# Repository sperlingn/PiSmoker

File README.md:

# PiSmoker

##Dependencies
* RPI.GPIO
* spidev
* [Adafruit_Python_CharLCD](https://github.com/adafruit/Adafruit_Python_CharLCD)
* [Python-firebase](https://github.com/ozgur/python-firebase) Use github version instead of pip

## Schematics and Boards
* PiSmoker_pwr_triac_isol -- AC handling board, includes SW PS for backpowering Raspi.
* PiSmoker_sig_v1.1 -- Signal boards, conforms to Pi HAT specifications, including EEPROM.

Signal board and power board for traic based control.  Includes board power with isolation and 4 triacs.  Signaling board has space for 1 RTD via MAX31865, 2 thermocouples (and internal temperature sensor) via ADS1118, and 2 thermocouples and 4 thermistor probes via MCP3208.  Using MAX31865 temperature for CJC for all thermocouples should be possible due to placement underneath connector.

## Work to be done

* TODO: Add support for firebox burnout sensor (purpose of TC1, hotbox TC to see if temp is >setpoint, will require testing temps).  Should be able to run igniter if it is sensed early enough without having to clear out the firebox of pellets or blow the temperature range.
* TODO: Add parsing of EEPROM settings.

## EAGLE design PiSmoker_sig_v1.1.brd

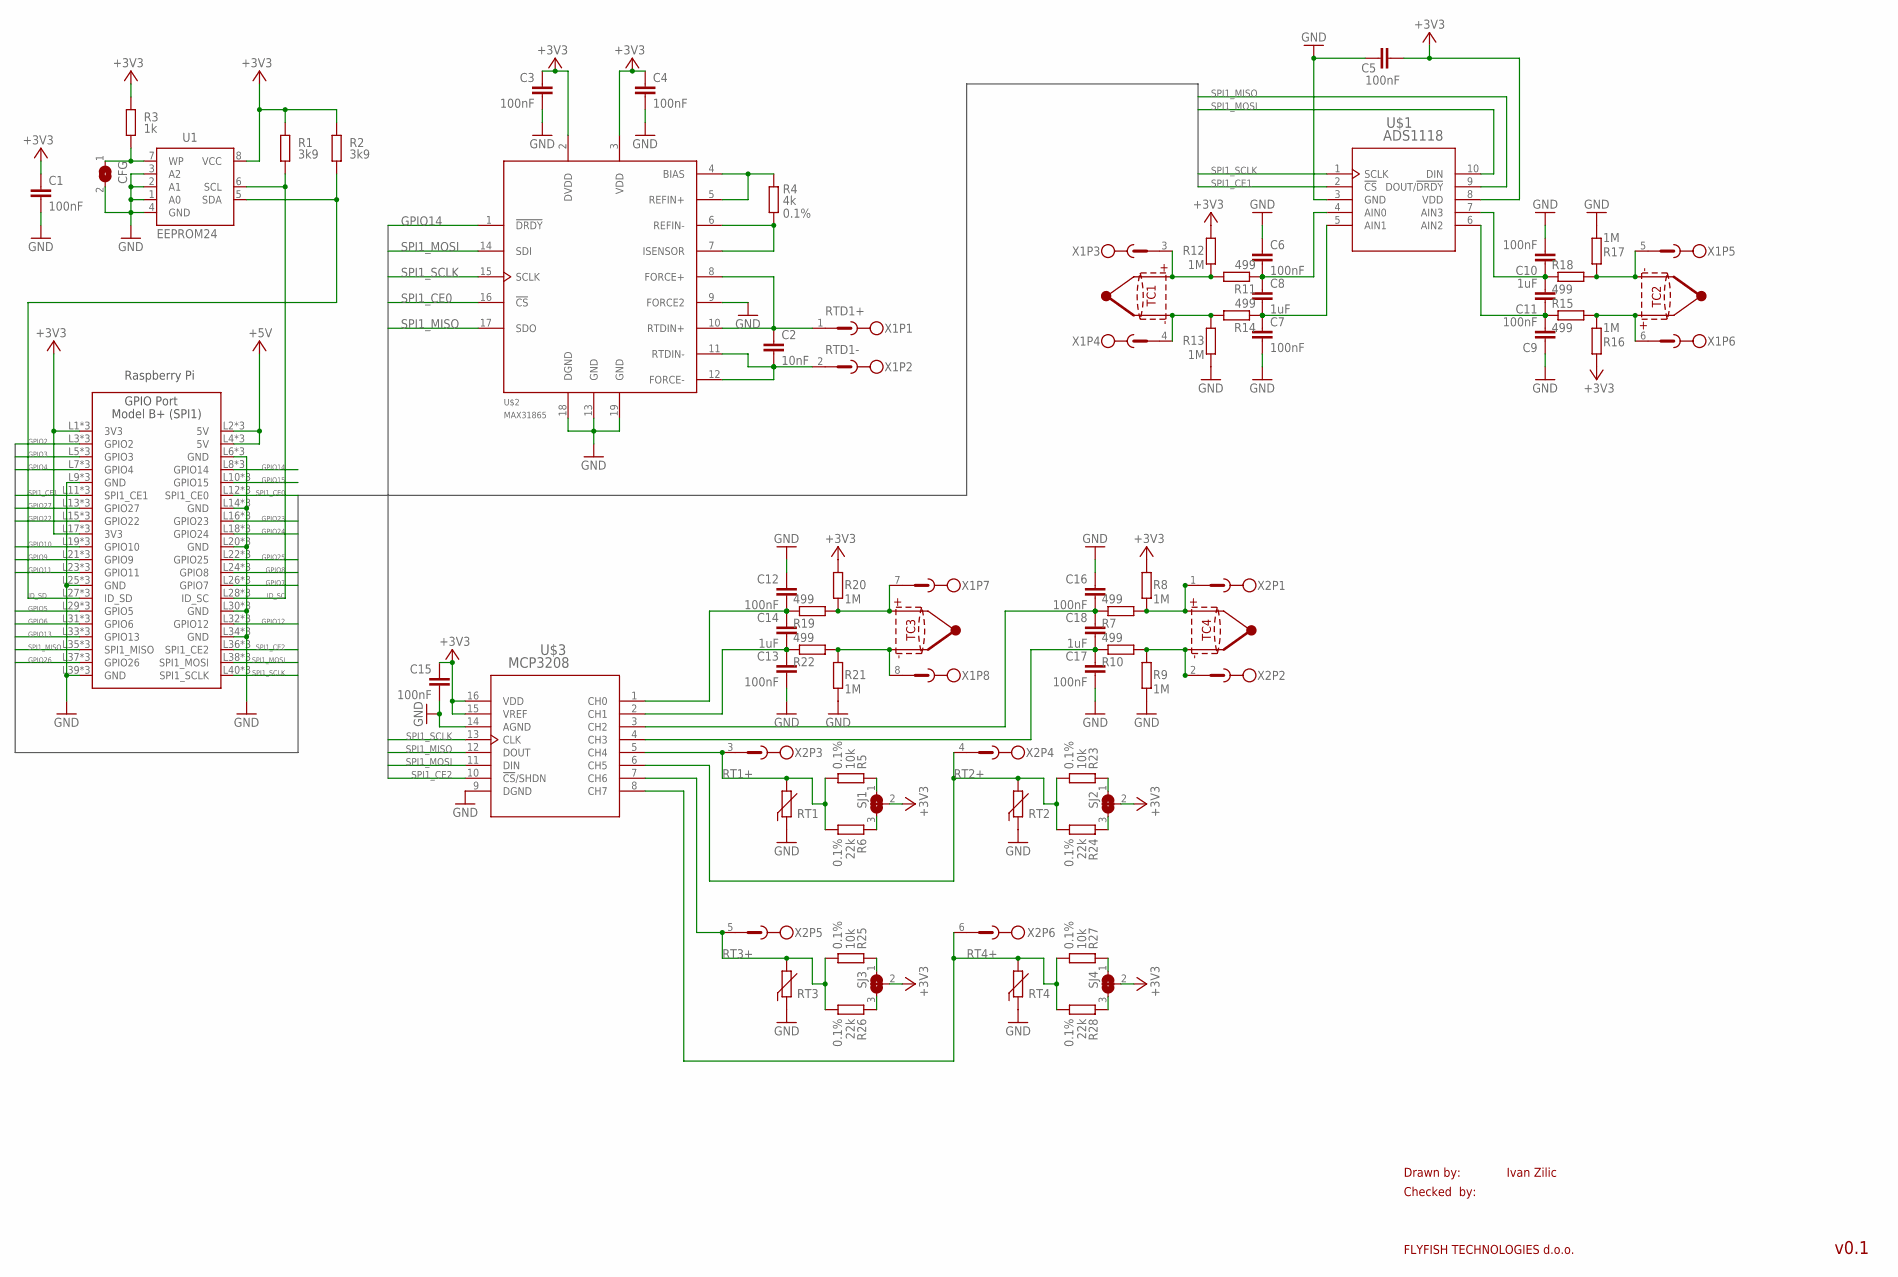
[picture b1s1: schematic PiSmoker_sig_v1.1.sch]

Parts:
C1, C3, C4, C5, C6, C7, C9, C10, C12, C13, C15, C16, C17: 100nF; C0805K
C2: 10nF; C0805
C8, C11, C14, C18: 1uF; C0805K
CFG: SOLDERJUMPERCLOSED; SOLDERJUMPER_CLOSEDWIRE
R1, R2: 3k9; M0805; TOLERANCE 5%
R3: 1k; M0805; TOLERANCE 5%
R4: 4k; R1206; TOLERANCE 0.1%
R5, R23, R25, R27: 10k; R0805; TOLERANCE 0.1%
R6, R24, R26, R28: 22k; R0805; TOLERANCE 0.1%
R7, R10, R11, R14, R15, R18, R19, R22: 499; M0805; TOLERANCE 5%
R8, R9, R12, R13, R16, R17, R20, R21: 1M; M0805; TOLERANCE 5%
SJ1, SJ2, SJ3, SJ4: SOLDERJUMPER_2WAY; SOLDERJUMPER_2WAY_ARROW_NOPASTE
U1: EEPROM24; SOIC8
U$1: ADS1118; DGS10
U$2: MAX31865; SSOP20_A20-1
U$3: MCP3208; SOIC16-N_MC
X1: TERMINAL_BLOCK-8PTSM0,5; PHOENIX_PTSM0,5/8-2,5-H_SMD_R44
X2: PHOENIX_PTS1,5-6PTSM0,5; PHOENIX_PTSM0,5/6-2,5-H_SMD_R44
X3: RASPI_GPIO_3B_SPI1_M20-781LOWER-876_UPPER; M20-781_SMD_LOWER_876_UPPER

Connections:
+3V3: C1.1, C3.1, C4.1, C5.2, C15.1, R1.2, R2.2, R3.2, R8.1, R12.1, R16.1, R20.1, SJ1.2, SJ2.2, SJ3.2, SJ4.2, U1.8 (VCC), U$1.8 (VDD), U$2.2 (DVDD), U$2.3 (VDD), U$3.15 (VREF), U$3.16 (VDD), X3.L1 (3V3), X3.L17 (3V3), X3.P1 (3V3), X3.P17 (3V3), X3.U1 (3V3), X3.U17 (3V3)
+5V: X3.L2 (5V), X3.L4 (5V), X3.P2 (5V), X3.P4 (5V), X3.U2 (5V), X3.U4 (5V)
GND: C1.2, C3.2, C4.2, C5.1, C6.1, C7.2, C9.1, C10.2, C12.1, C13.2, C15.2, C16.1, C17.2, CFG.2, R9.2, R13.2, R17.2, R21.2, U1.1 (A0), U1.2 (A1), U1.3 (A2), U1.4 (GND), U$1.3 (GND), U$2.9 (FORCE2), U$2.13 (GND), U$2.18 (DGND), U$2.19 (GND), U$3.9 (DGND), U$3.14 (AGND), X3.L6 (GND), X3.L9 (GND), X3.L14 (GND), X3.L20 (GND), X3.L25 (GND), X3.L30 (GND), X3.L34 (GND), X3.L39 (GND), X3.P6 (GND), X3.P9 (GND), X3.P14 (GND), X3.P20 (GND), X3.P25 (GND), X3.P30 (GND), X3.P34 (GND), X3.P39 (GND), X3.U6 (GND), X3.U9 (GND), X3.U14 (GND), X3.U20 (GND), X3.U25 (GND), X3.U30 (GND), X3.U34 (GND), X3.U39 (GND)
GPIO2: X3.L3 (GPIO2), X3.P3 (GPIO2), X3.U3 (GPIO2)
GPIO3: X3.L5 (GPIO3), X3.P5 (GPIO3), X3.U5 (GPIO3)
GPIO4: X3.L7 (GPIO4), X3.P7 (GPIO4), X3.U7 (GPIO4)
GPIO5: X3.L29 (GPIO5), X3.P29 (GPIO5), X3.U29 (GPIO5)
GPIO6: X3.L31 (GPIO6), X3.P31 (GPIO6), X3.U31 (GPIO6)
GPIO7: X3.L26 (GPIO7), X3.P26 (GPIO7), X3.U26 (GPIO7)
GPIO8: X3.L24 (GPIO8), X3.P24 (GPIO8), X3.U24 (GPIO8)
GPIO9: X3.L21 (GPIO9), X3.P21 (GPIO9), X3.U21 (GPIO9)
GPIO10: X3.L19 (GPIO10), X3.P19 (GPIO10), X3.U19 (GPIO10)
GPIO11: X3.L23 (GPIO11), X3.P23 (GPIO11), X3.U23 (GPIO11)
GPIO12: X3.L32 (GPIO12), X3.P32 (GPIO12), X3.U32 (GPIO12)
GPIO13: X3.L33 (GPIO13), X3.P33 (GPIO13), X3.U33 (GPIO13)
GPIO14: U$2.1 (!DRDY), X3.L8 (GPIO14), X3.P8 (GPIO14), X3.U8 (GPIO14)
GPIO15: X3.L10 (GPIO15), X3.P10 (GPIO15), X3.U10 (GPIO15)
GPIO22: X3.L15 (GPIO22), X3.P15 (GPIO22), X3.U15 (GPIO22)
GPIO23: X3.L16 (GPIO23), X3.P16 (GPIO23), X3.U16 (GPIO23)
GPIO24: X3.L18 (GPIO24), X3.P18 (GPIO24), X3.U18 (GPIO24)
GPIO25: X3.L22 (GPIO25), X3.P22 (GPIO25), X3.U22 (GPIO25)
GPIO26: X3.L37 (GPIO26), X3.P37 (GPIO26), X3.U37 (GPIO26)
GPIO27: X3.L13 (GPIO27), X3.P13 (GPIO27), X3.U13 (GPIO27)
ID_SC: R1.1, U1.6 (SCL), X3.L28 (ID_SC), X3.P28 (ID_SC), X3.U28 (ID_SC)
ID_SD: R2.1, U1.5 (SDA), X3.L27 (ID_SD), X3.P27 (ID_SD), X3.U27 (ID_SD)
unnamed: C7.1, C8.2, R14.1, U$1.5 (AIN1)
unnamed: C6.2, C8.1, R11.1, U$1.4 (AIN0)
unnamed: CFG.1, R3.1, U1.7 (WP)
unnamed: R5.2, SJ1.1
unnamed: R6.2, SJ1.3
unnamed: C17.1, C18.2, R10.1, U$3.4 (CH3)
unnamed: C16.2, C18.1, R7.1, U$3.3 (CH2)
unnamed: R23.2, SJ2.1
unnamed: R24.2, SJ2.3
unnamed: R25.2, SJ3.1
unnamed: R4.2, U$2.4 (BIAS), U$2.5 (REFIN+)
unnamed: R4.1, U$2.6 (REFIN-), U$2.7 (ISENSOR)
unnamed: C13.1, C14.2, R22.1, U$3.2 (CH1)
unnamed: C12.2, C14.1, R19.1, U$3.1 (CH0)
unnamed: C10.1, C11.2, R18.1, U$1.7 (AIN3)
unnamed: C9.2, C11.1, R15.1, U$1.6 (AIN2)
unnamed: R26.2, SJ3.3
unnamed: R27.2, SJ4.1
unnamed: R28.2, SJ4.3
RT1+: R5.1, R6.1, U$3.5 (CH4), X2.3
RT2+: R23.1, R24.1, U$3.6 (CH5), X2.4
RT3+: R25.1, R26.1, U$3.7 (CH6), X2.5
RT4+: R27.1, R28.1, U$3.8 (CH7), X2.6
RTD1+: C2.1, U$2.8 (FORCE+), U$2.10 (RTDIN+), X1.1
RTD1-: C2.2, U$2.11 (RTDIN-), U$2.12 (FORCE-), X1.2
SPI1_CE0: U$2.16 (!CS), X3.L12 (SPI1_CE0), X3.P12 (SPI1_CE0), X3.U12 (SPI1_CE0)
SPI1_CE1: U$1.2 (!CS), X3.L11 (SPI1_CE1), X3.P11 (SPI1_CE1), X3.U11 (SPI1_CE1)
SPI1_CE2: U$3.10 (!CS!/SHDN), X3.L36 (SPI1_CE2), X3.P36 (SPI1_CE2), X3.U36 (SPI1_CE2)
SPI1_MISO: U$1.9 (DOUT/!DRDY), U$2.17 (SDO), U$3.12 (DOUT), X3.L35 (SPI1_MISO), X3.P35 (SPI1_MISO), X3.U35 (SPI1_MISO)
SPI1_MOSI: U$1.10 (DIN), U$2.14 (SDI), U$3.11 (DIN), X3.L38 (SPI1_MOSI), X3.P38 (SPI1_MOSI), X3.U38 (SPI1_MOSI)
SPI1_SCLK: U$1.1 (SCLK), U$2.15 (SCLK), U$3.13 (CLK), X3.L40 (SPI1_SCLK), X3.P40 (SPI1_SCLK), X3.U40 (SPI1_SCLK)
TC1+: R11.2, R12.2, X1.3
TC1-: R13.1, R14.2, X1.4
TC2+: R17.1, R18.2, X1.5
TC2-: R15.2, R16.2, X1.6
TC3+: R19.2, R20.2, X1.7
TC3-: R21.1, R22.2, X1.8
TC4+: R7.2, R8.2, X2.1
TC4-: R9.1, R10.2, X2.2

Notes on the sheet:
Drawn by:
Checked by:
FLYFISH TECHNOLOGIES d.o.o.
Ivan Zilic
v0.1

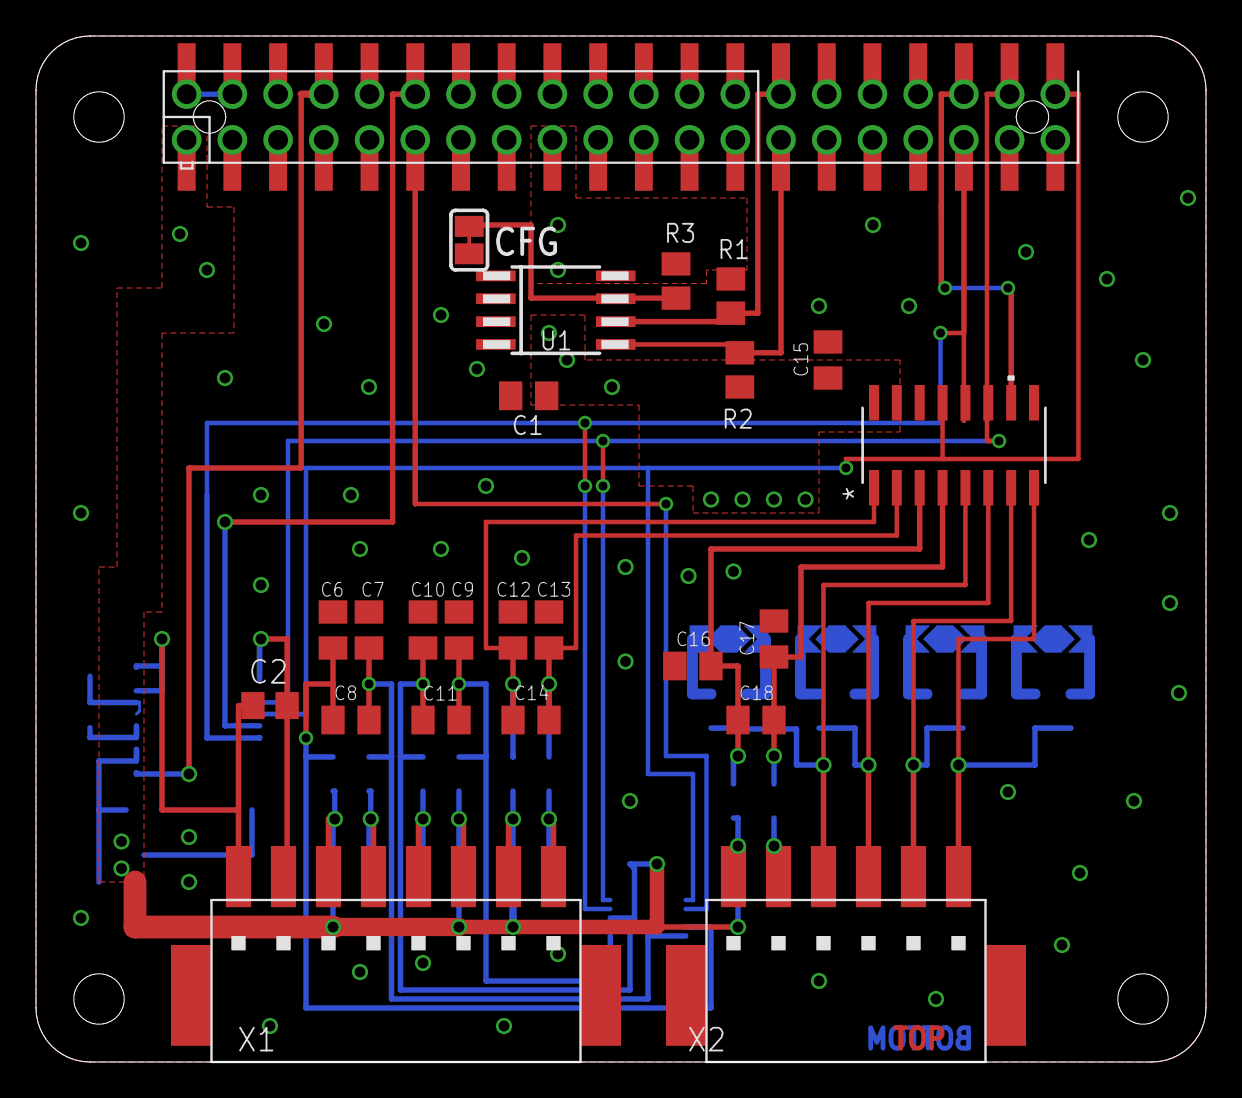
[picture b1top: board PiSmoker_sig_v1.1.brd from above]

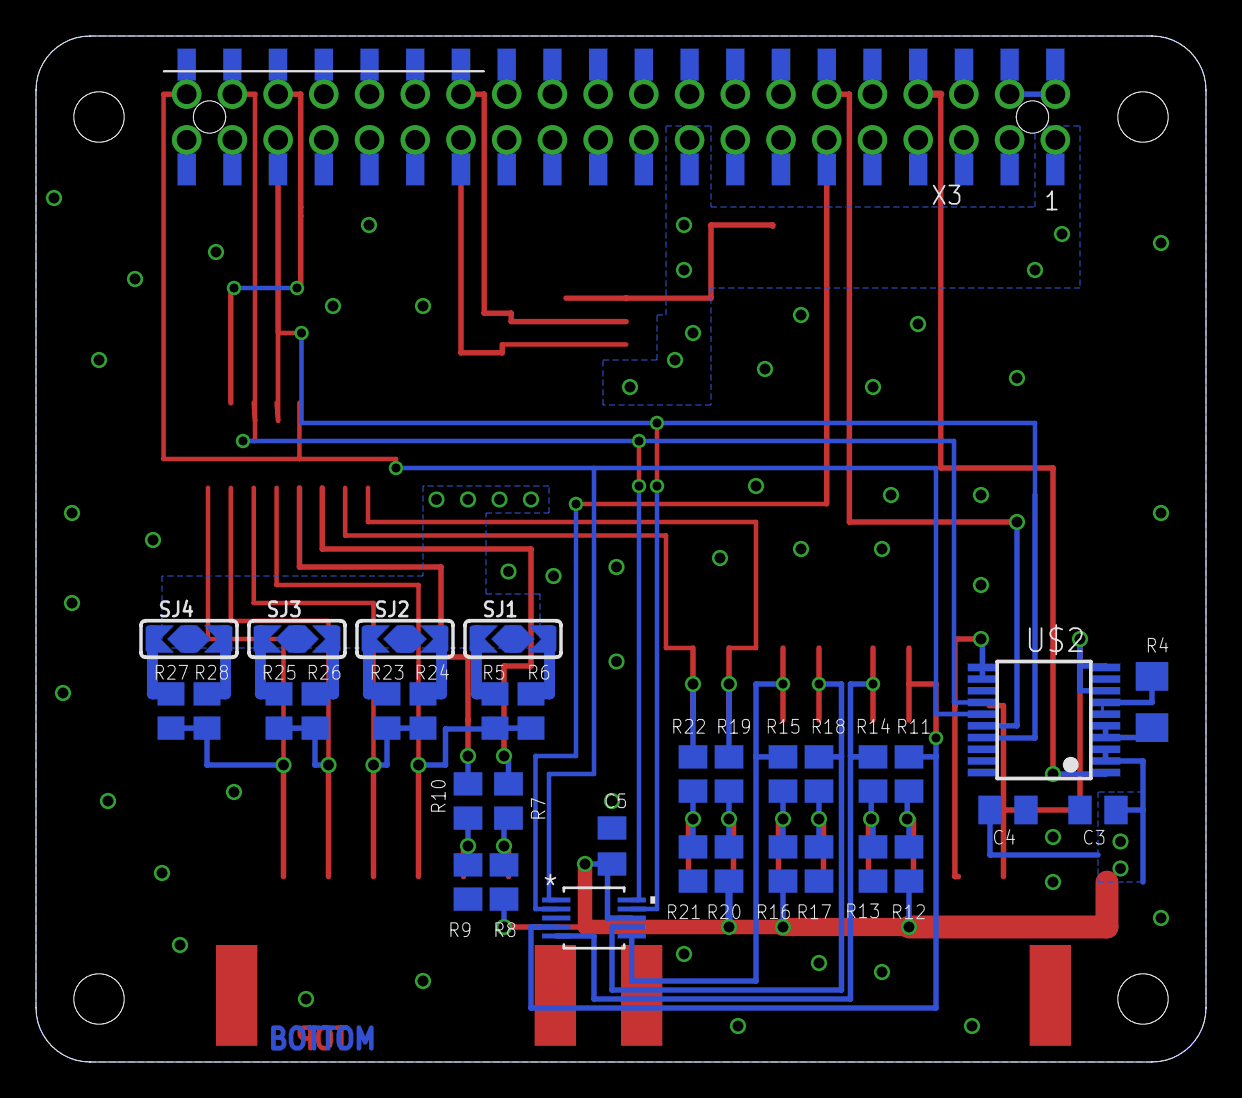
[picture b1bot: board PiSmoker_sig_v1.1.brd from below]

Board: 2 copper layers, 65.0 x 57.0 mm, 58 parts (34 on the bottom side), 64 nets.

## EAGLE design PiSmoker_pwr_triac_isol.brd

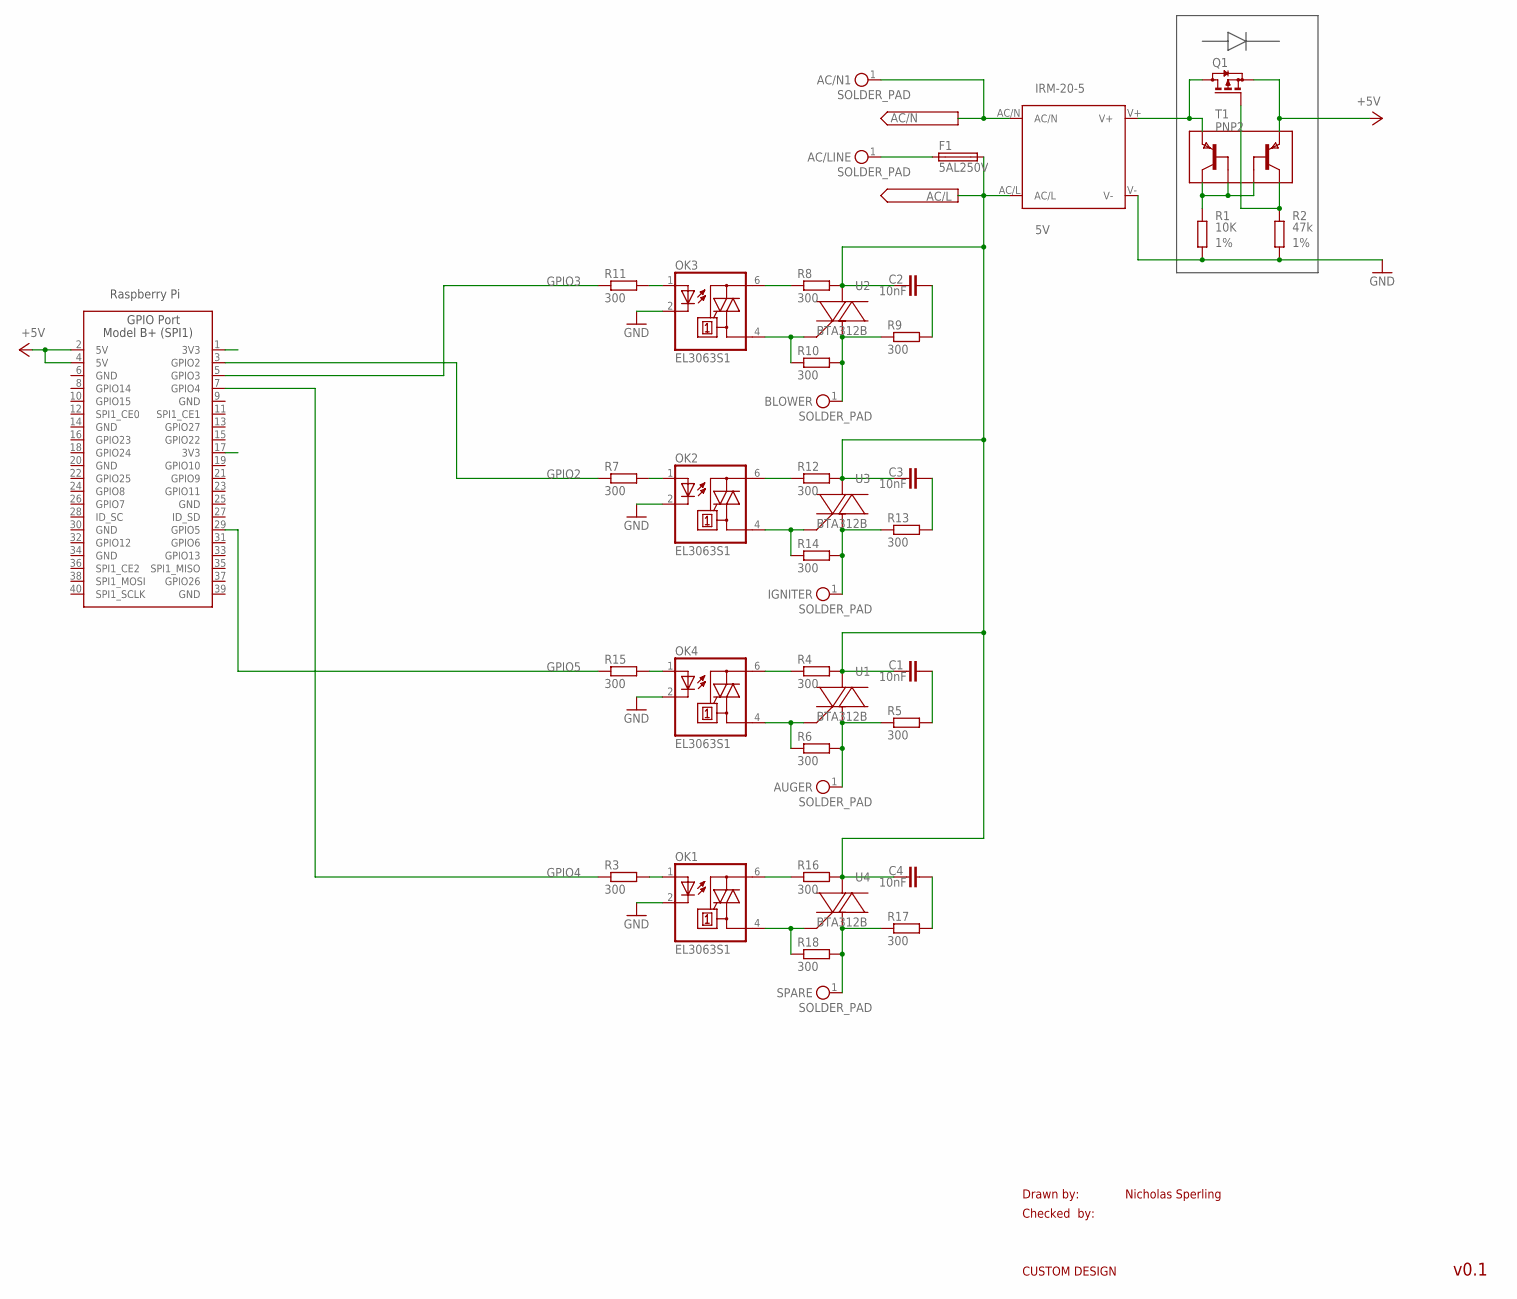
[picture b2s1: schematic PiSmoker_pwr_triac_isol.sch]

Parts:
AC/LINE: SOLDER_PAD; SOLDER_PAD_18AWG
AC/N1: SOLDER_PAD; SOLDER_PAD_18AWG
AUGER: SOLDER_PAD; SOLDER_PAD_18AWG
BLOWER: SOLDER_PAD; SOLDER_PAD_18AWG
C1, C2, C3, C4: 10nF; C1206
F1: 5AL250V; OGN_SMD
IGNITER: SOLDER_PAD; SOLDER_PAD_18AWG
IRM-20-5: 5V; IRM_15/20
OK1, OK2, OK3, OK4: EL3063S1; SMD6
Q1: BSS84; SOT23
R1: 10K; M0805; TOLERANCE 1%
R2: 47k; M0805; TOLERANCE 1%
R3, R4, R5, R6, R7, R8, R9, R10, R11, R12, R13, R14, R15, R16, R17, R18: 300; M0805; TOLERANCE 5%
SPARE: SOLDER_PAD; SOLDER_PAD_18AWG
T1: PNP2; SOT26
U1, U2, U3, U4: BTA312B; D2PAK-3
X1: RASPI_GPIO_3B_SPI1_M20-781_SMD_LOWER_NOHOLES; M20-781_SMD_LOWER_NOHOLES

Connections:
+5V: Q1.2 (S), T1.5 (E2), X1.2 (5V), X1.4 (5V)
AC/L: C1.1, C2.1, C3.1, C4.1, F1.2, IRM-20-5.AC/L, R4.2, R8.2, R12.2, R16.2, U1.MB (MT2), U2.MB (MT2), U3.MB (MT2), U4.MB (MT2)
AC/N: AC/N1.1, IRM-20-5.AC/N
AUGER_AC/L: AUGER.1, R5.1, R6.2, U1.1 (MT1)
BLOWER_AC/L: BLOWER.1, R9.1, R10.2, U2.1 (MT1)
GND: IRM-20-5.V-, OK1.2 (C), OK2.2 (C), OK3.2 (C), OK4.2 (C), R1.1, R2.1, X1.6 (GND), X1.9 (GND), X1.14 (GND), X1.20 (GND), X1.25 (GND), X1.30 (GND), X1.34 (GND), X1.39 (GND)
GPIO2: R7.1, X1.3 (GPIO2)
GPIO3: R11.1, X1.5 (GPIO3)
GPIO4: R3.1, X1.7 (GPIO4)
GPIO5: R15.1, X1.29 (GPIO5)
IGNITER_AC/L: IGNITER.1, R13.1, R14.2, U3.1 (MT1)
unnamed: C1.2, R5.2
unnamed: OK1.1 (A), R3.2
unnamed: C2.2, R9.2
unnamed: OK3.6 (A2), R8.1
unnamed: OK3.4 (A1), R10.1, U2.3 (G)
unnamed: OK2.1 (A), R7.2
unnamed: OK2.4 (A1), R14.1, U3.3 (G)
unnamed: OK2.6 (A2), R12.1
unnamed: C3.2, R13.2
unnamed: OK3.1 (A), R11.2
unnamed: OK4.6 (A2), R4.1
unnamed: IRM-20-5.V+, Q1.3 (D), T1.6 (E1)
unnamed: Q1.1 (G), R2.2, T1.4 (C2)
unnamed: R1.2, T1.1 (C1), T1.2 (B1), T1.3 (B2)
unnamed: OK4.4 (A1), R6.1, U1.3 (G)
unnamed: C4.2, R17.2
unnamed: OK4.1 (A), R15.2
unnamed: OK1.4 (A1), R18.1, U4.3 (G)
unnamed: OK1.6 (A2), R16.1
unnamed: AC/LINE.1, F1.1
SPARE_AC/L: R17.1, R18.2, SPARE.1, U4.1 (MT1)

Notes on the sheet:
Drawn by:
Checked by:
CUSTOM DESIGN
Nicholas Sperling
v0.1

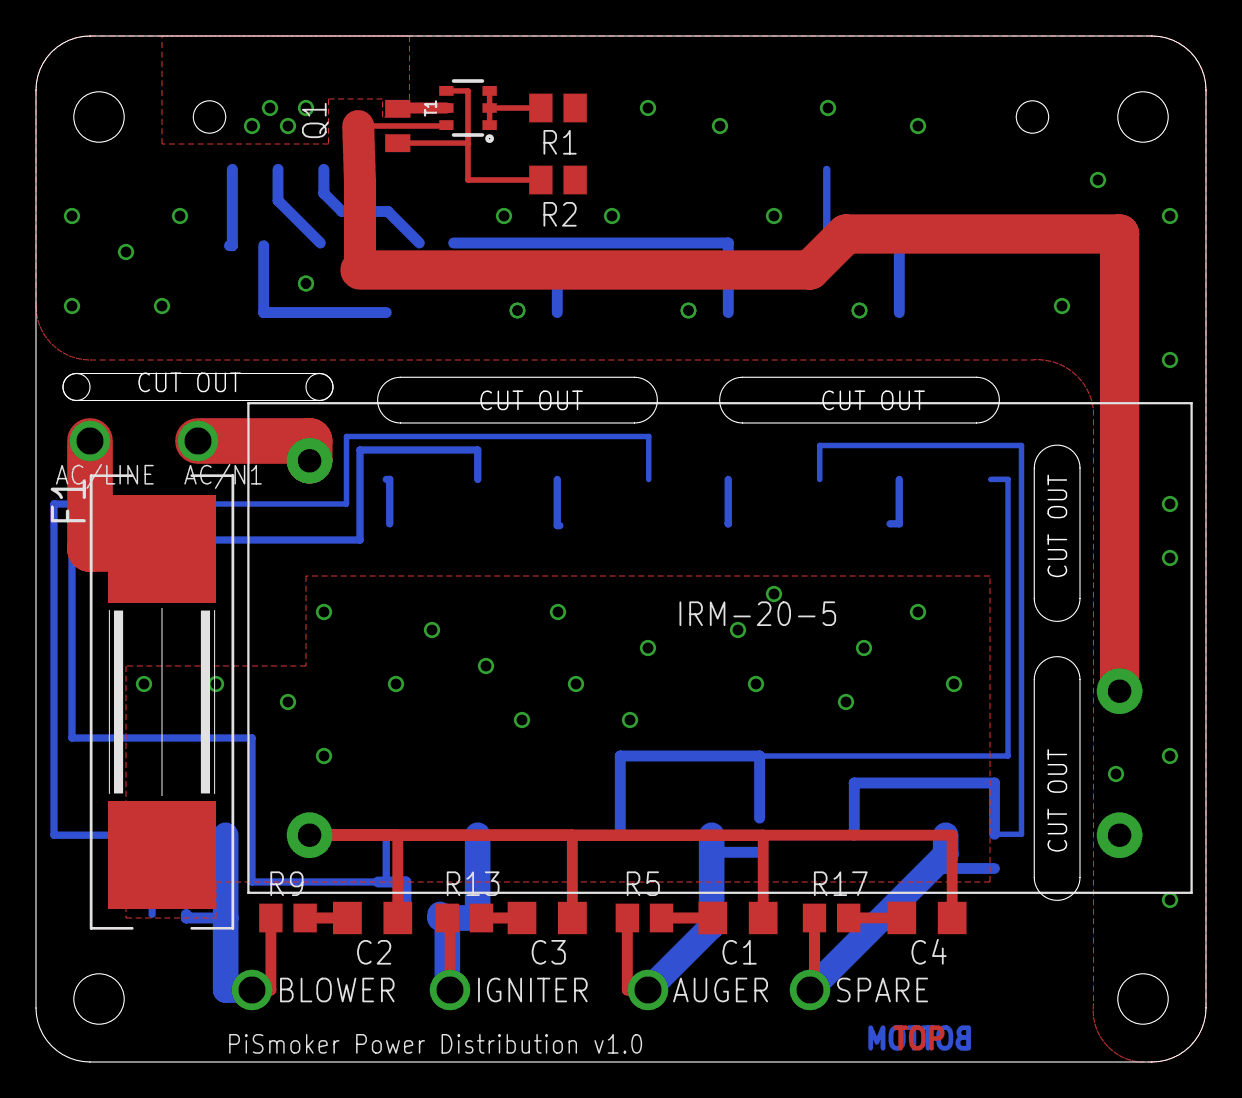
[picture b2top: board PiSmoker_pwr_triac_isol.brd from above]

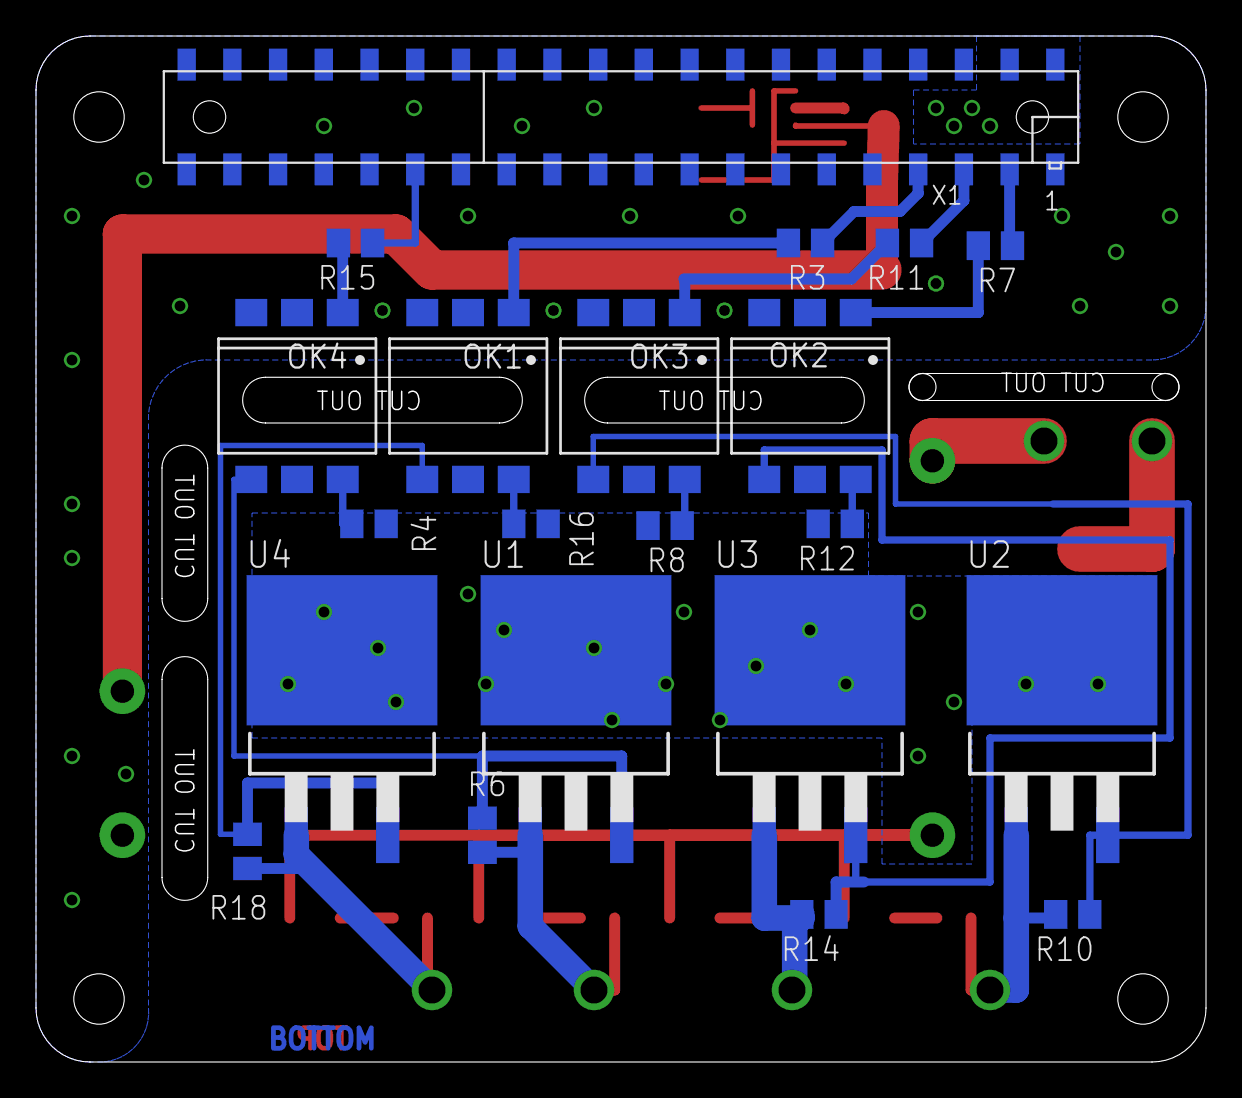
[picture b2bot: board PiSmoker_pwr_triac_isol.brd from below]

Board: 2 copper layers, 65.0 x 57.0 mm, 41 parts (20 on the bottom side), 32 nets.

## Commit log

2015-12-01 Added program.
2015-12-01 Removed timestamp
2015-12-01 Added pulling the program
2015-12-01 Moved last time
2015-12-01 Syntax
2015-12-01 Added logging
2015-12-01 Added program evaluation
2015-12-01 Added async writing
2015-12-02 Added stopping the program
2015-12-02 Updated writing program.
2015-12-02 Deubgging
2015-12-02 Search for new programs before starting.
2015-12-02 Only check for new programs if running
2015-12-02 Parameter
2015-12-02 Add a little delay after starting the program
2015-12-02 Fixed ReadParameters return on failure
2016-01-03 Added additional tenth to display
2016-01-11 Moved a WriteParameters to avoid constant updates.
2016-01-11 Added set mode after PMode changes.
2016-01-30 Added 3 wire configuration
2016-01-31 Added constant igniter on for start mode
2016-01-31 Changed debugging level
2016-01-31 Changed start back to 115.
2016-03-19 Added ignite mode
2016-03-28 Fixed config for MAX31865 for 3 wire configuration
2016-04-10 Added manifest to add to homescreen
2016-04-16 Reverted to old files
2016-04-16 moved files
2016-04-16 Updated manifest
2016-04-16 Changed manifest mode
2016-04-16 Added manifest
2016-06-12 Added limit to history
2017-01-08 Uploaded schematic and board files for PiSmoker
    Signal board and power board for traic based control. Includes board power with isolation and 4 triacs. Signaling board has space for 1 RTD via MAX31865, 2 thermocouples (and internal temperature sen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
2017-01-08 Update README.md
    Describe changes and TODO.
2017-01-08 Add BOM and ordering details for mouser.
    Bill of materials, placement details, and mouser part numbers with messup margins.
2017-01-13 Update TODO, begin trager class rework, including option for GPIO inversion.
2017-01-13 removed IDE files from server
2017-01-16 Begin implementing new classes for various ADCs in use.
2017-01-17 Work on new generic temperature probe class, incl. thermocouple data.
2017-01-18 Continue implementation of ADC chips and temperature probe class.
2017-01-18 Continue refactoring on main code.
2017-01-20 Refactored into class, begin board specific implementation.
2017-01-26 Bugfix in TemperatureProbe and ASD1118 (^ is XOR not **) Added per channel gain for ADS1118
2017-01-26 Continue refactor of main code. Changing handling of temperature log (only hold the temps needed in memory and implement a rolling average class)
2017-01-29 Created EEPROM settings.
2017-02-02 Debugging interfaces. Bug in SpiDev requires bitbanged SPI for ADS1118. Lots of bug fixes.

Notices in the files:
parts and their libraries:
COPYRIGHT: Copyright C 2015 Accelerated Designs. All rights reserved
